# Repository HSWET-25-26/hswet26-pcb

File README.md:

Only edited schematic
Deleted 6v back converter

Schematic
- [x] 1x5 connecter -> 1x4 connector, deleted 6v line
- [x] Resistor and diode are swapped make sure they are swapped - on safety page
- [x] 5V_BUCK label should be 4.5V_BUCK

PCB
- [ ] Trace sizes
    - [ ] Check what gauge traces going into ina (lol it's not nearly what I fixed it for but might as well keep it)
    - [ ] Use larger trace sizes if possible though, no reason not too. And power planes for 9V and turbine for extra safety
- [X] Both of the LM2596 replace with full board
    - [X] Deleted 6v buck converter
- [ ] Add pads for debugging
    - [ ] add Nets:
        - [ ] Linear actuator signal (D5)
        - [ ] Encoder (D2)
        - [ ] Safety signal (D4)
        - [ ] Turbine power 
        - [ ] Lowkey everything there’s not that many nets
- [ ] Add labels to everything!!! on the board! make it as clear as possible
- [ ] Things to double check b/c Mirabel thinks she routed it wrong:
    - [ ] vias on 2 ground pins on U4

- [ ] Add holes on corners for default m3 screws

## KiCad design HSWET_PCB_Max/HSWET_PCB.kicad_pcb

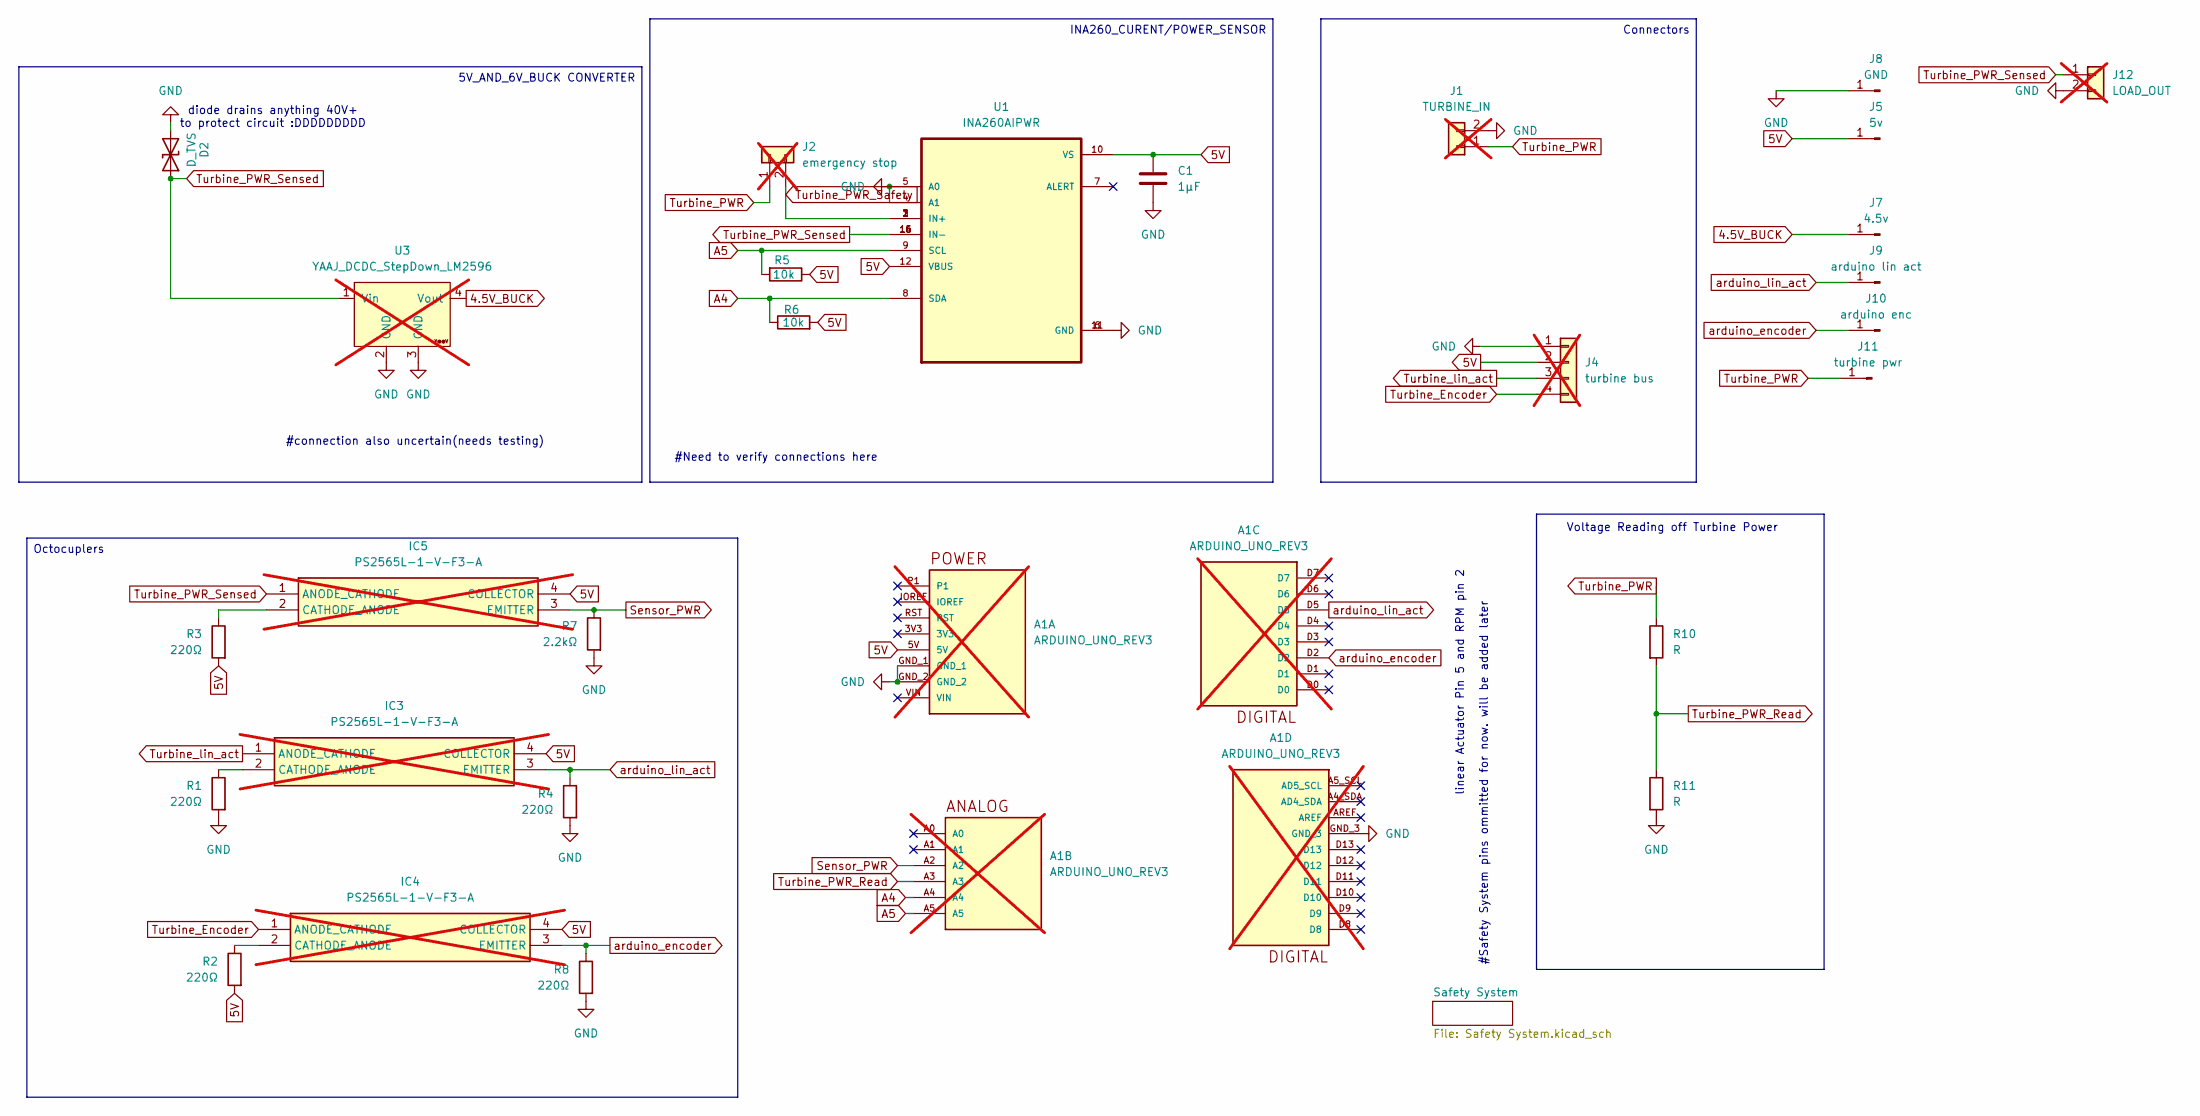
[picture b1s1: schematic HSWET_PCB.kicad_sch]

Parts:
A1: ARDUINO_UNO_REV3; ARDUINO_ARDUINO_UNO_REV3; PARTREV N/A; not fitted
C1: 1µF; C_0603_1608Metric
D2: D_TVS; DIOM4336X265N
IC3, IC4, IC5: PS2565L-1-V-F3-A; DIP762W60P254L460H455Q4N; Manufacturer_Part_Number PS2565L-1-V-F3-A; Mouser Part Number 968-PS2565L-1-V-F3-A; not fitted
J1: TURBINE_IN; AMASS_XT30PW-M_1x02_P2.50mm_Horizontal; not fitted
J2: emergency stop; JST_EH_B2B-EH-A_1x02_P2.50mm_Vertical; not fitted
J4: turbine bus; PinHeader_1x04_P2.54mm_Horizontal; not fitted
J5: 5v; PinHeader_1x01_P1.00mm_Vertical
J7: 4.5v; PinHeader_1x01_P1.00mm_Vertical
J8: GND; PinHeader_1x01_P1.00mm_Vertical
J9: arduino lin act; PinHeader_1x01_P1.00mm_Vertical
J10: arduino enc; PinHeader_1x01_P1.00mm_Vertical
J11: turbine pwr; PinHeader_1x01_P1.00mm_Vertical
J12: LOAD_OUT; AMASS_XT30PW-M_1x02_P2.50mm_Horizontal; not fitted
R1, R2, R3, R4, R8: 220Ω; R_0603_1608Metric
R5, R6: 10k; R_0603_1608Metric
R7: 2.2kΩ; R_0603_1608Metric
R10, R11: R; R_Axial_DIN0207_L6.3mm_D2.5mm_P10.16mm_Horizontal
U1: INA260AIPWR; ina260
U3: YAAJ_DCDC_StepDown_LM2596; not fitted

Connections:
4.5V_BUCK: J7.1, U3.4 (Vout); also elsewhere on the board
A4: A1.A4, R6.1, U1.8 (SDA)
A5: A1.A5, R5.2, U1.9 (SCL)
unnamed: IC3.2 (CATHODE_ANODE), R1.1
unnamed: IC4.2 (CATHODE_ANODE), R2.1
unnamed: IC5.2 (CATHODE_ANODE), R3.1
Sensor_PWR: A1.A2, IC5.3 (EMITTER), R7.1
Turbine_Encoder: IC4.1 (ANODE_CATHODE), J4.4
Turbine_PWR: J1.1, J2.1, J11.1, R10.1
Turbine_PWR_Read: A1.A3, R10.2, R11.1
Turbine_PWR_Safety: J2.2, U1.1 (IN+), U1.2 (IN+), U1.3 (IN+)
Turbine_PWR_Sensed: D2.1 (A1), IC5.1 (ANODE_CATHODE), J12.1, U1.14 (IN-), U1.15 (IN-), U1.16 (IN-), U3.1 (Vin)
Turbine_lin_act: IC3.1 (ANODE_CATHODE), J4.3
arduino_encoder: A1.D2, IC4.3 (EMITTER), J10.1, R8.1
arduino_lin_act: A1.D5, IC3.3 (EMITTER), J9.1, R4.1

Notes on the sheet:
#Safety System pins ommitted for now. will be added later
#Need to verify connections here
#connection also uncertain(needs testing)
linear Actuator Pin 5 and RPM pin 2
Voltage Reading off Turbine Power
diode drains anything 40V+ to protect circuit :DDDDDDDDD
Octocuplers
Connectors
5V_AND_6V_BUCK CONVERTER
INA260_CURENT/POWER_SENSOR

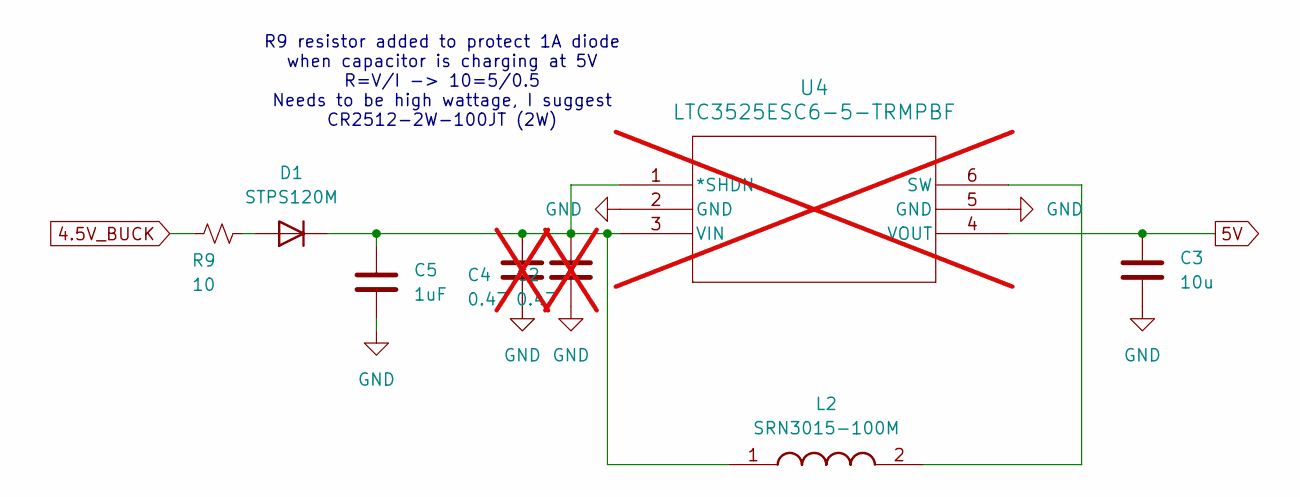
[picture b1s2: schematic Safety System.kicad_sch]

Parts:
C2, C4: 0.47; CAPPRD500W60D1000H3150; not fitted
C3: 10u; C_0603_1608Metric
C5: 1uF; C_0603_1608Metric
D1: STPS120M; DIO_STPS1L40M
L2: SRN3015-100M; SRN3015; Manufacturer_Part_Number SRN3015-100M
R9: 10; R_2512_6332Metric
U4: LTC3525ESC6-5-TRMPBF; SC70-SC6_LIT; not fitted

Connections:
4.5V_BUCK: R9.1; also elsewhere on the board
unnamed: D1.2 (A), R9.2
unnamed: C2.1, C4.1, C5.1, D1.1 (K), L2.1, U4.1 (*SHDN), U4.3 (VIN)
unnamed: L2.2, U4.6 (SW)

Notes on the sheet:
R9 resistor added to protect 1A diode when capacitor is charging at 5V R=V/I -> 10=5/0.5 Needs to be high wattage, I suggest CR2512-2W-100JT (2W)

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
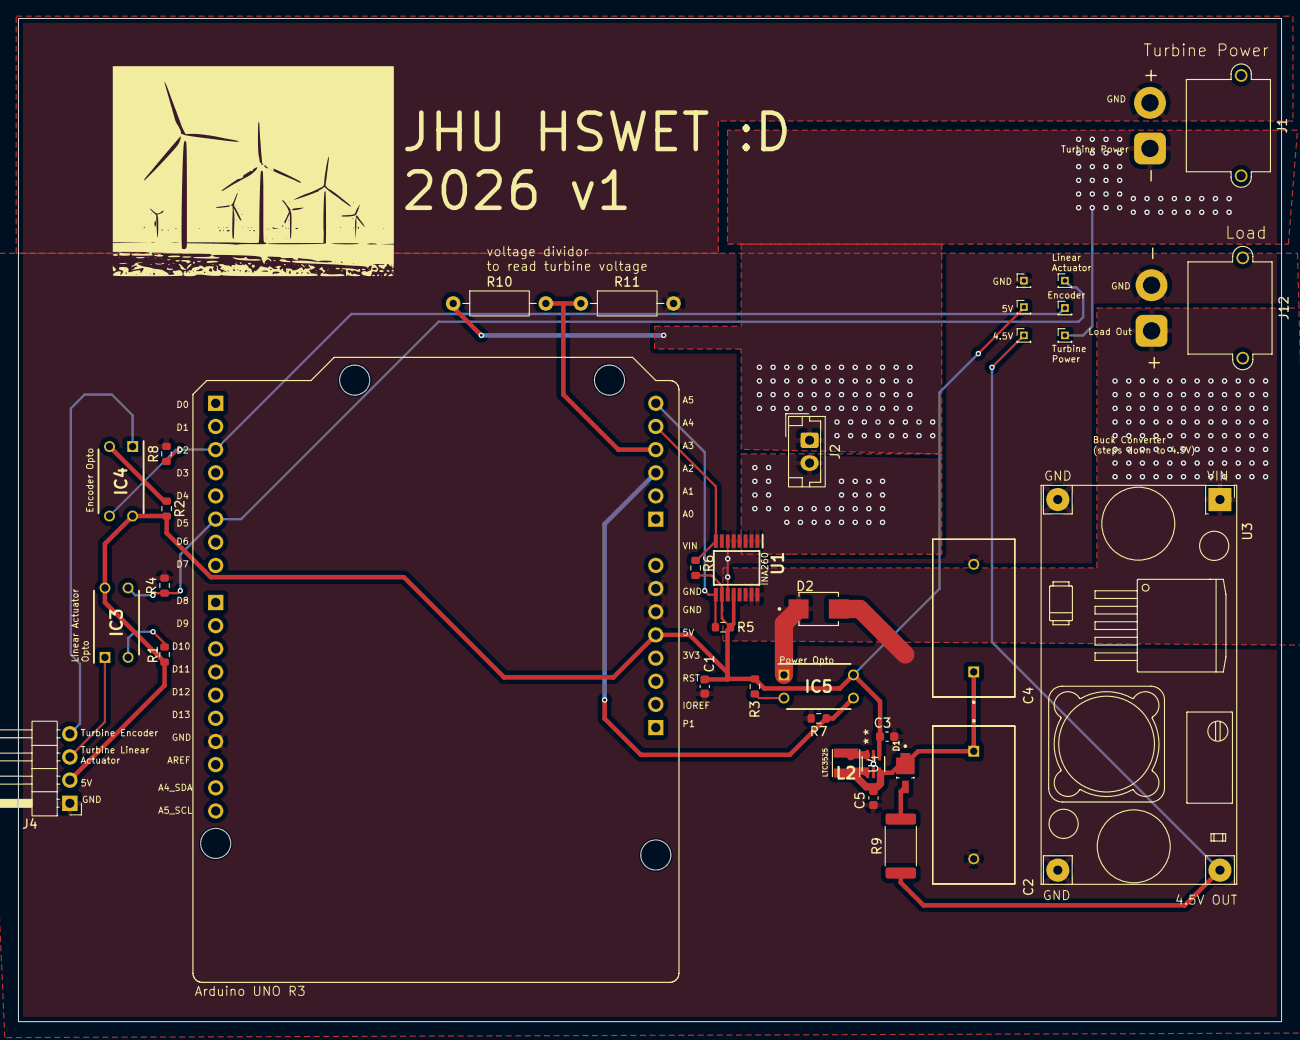
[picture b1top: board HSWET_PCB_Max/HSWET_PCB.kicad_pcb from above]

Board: 2 copper layers, 138.5 x 110.0 mm, 36 parts (0 on the bottom side), 20 nets.

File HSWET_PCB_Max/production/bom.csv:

Designator,Footprint,Quantity,Value,LCSC Part #
C1,0603,1,1µF,
C3,0603,1,10u,
C5,0603,1,1uF,
D1,DIO_STPS1L40M,1,STPS120M,
D2,DIOM4336X265N,1,D_TVS,
J10,PinHeader_1x01_P1.00mm_Vertical,1,arduino enc,
J11,PinHeader_1x01_P1.00mm_Vertical,1,turbine pwr,
J5,PinHeader_1x01_P1.00mm_Vertical,1,5v,
J7,PinHeader_1x01_P1.00mm_Vertical,1,4.5v,
J8,PinHeader_1x01_P1.00mm_Vertical,1,GND,
J9,PinHeader_1x01_P1.00mm_Vertical,1,arduino lin act,
L2,SRN3015,1,SRN3015-100M,
"R1, R2, R3, R4, R8",0603,5,220Ω,
"R10, R11",R_Axial_DIN0207_L6.3mm_D2.5mm_P10.16mm_Horizontal,2,R,
"R5, R6",0603,2,10k,
R7,0603,1,2.2kΩ,
R9,2512,1,10,
U1,ina260,1,INA260AIPWR,

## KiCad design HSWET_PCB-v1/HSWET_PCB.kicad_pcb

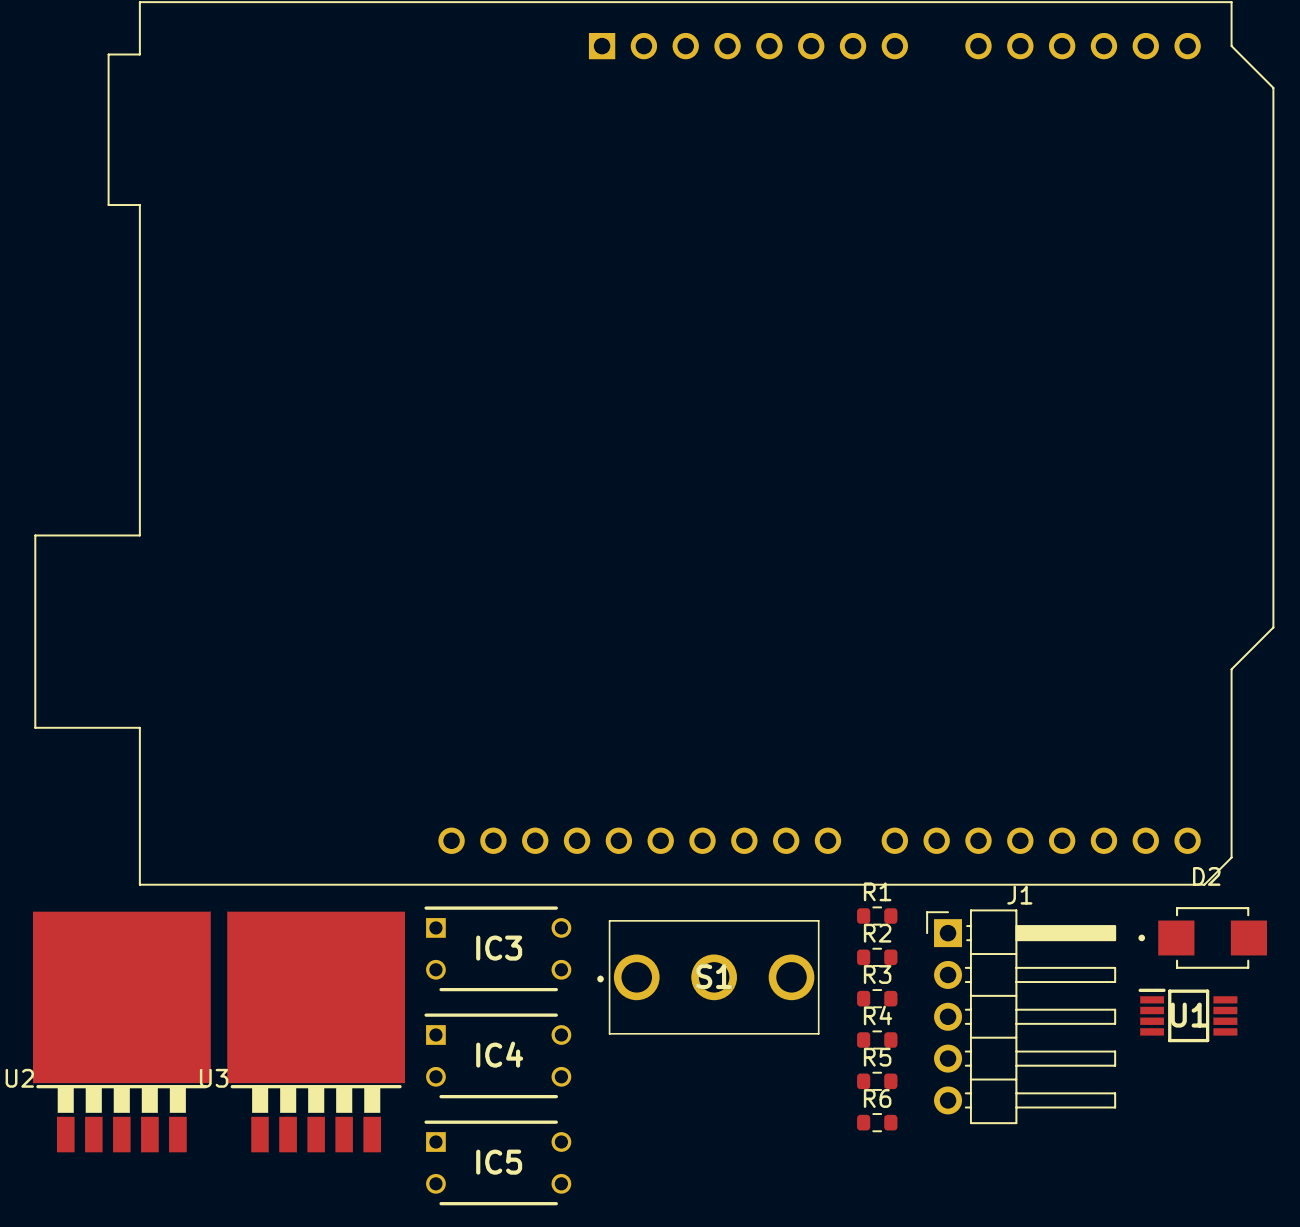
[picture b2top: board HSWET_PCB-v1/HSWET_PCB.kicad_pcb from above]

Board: 2 copper layers, 16 parts (0 on the bottom side), 14 nets, no tracks yet.

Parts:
A1: ARDUINO_UNO_REV3; Arduino_UNO_R3
D2: D_TVS; DIOM4336X265N
IC3, IC4, IC5: PS2565L-1-V-F3-A; DIP762W60P254L460H455Q4N
J1: Conn_01x05_Pin; PinHeader_1x05_P2.54mm_Horizontal
R1, R2, R3, R4, R5, R6: R; R_0603_1608Metric
S1: 100SP1T1B4M2QE
U1: INA260AIPWR; SOP65P490X110-8N
U2, U3: YAAJ_DCDC_StepDown_LM2596; TO263-5

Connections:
5V: IC3.4 (COLLECTOR), IC4.4 (COLLECTOR), J1.2, R1.2, R2.2, R5.2, U3.4 (Vout)
6V: J1.5, U2.4 (Vout)
GND: D2.2 (A2), IC3.1 (ANODE_CATHODE), IC4.1 (ANODE_CATHODE), IC5.1 (ANODE_CATHODE), J1.1, U1.6 (GND), U2.2 (GND), U2.3 (GND), U3.2 (GND), U3.3 (GND)
unnamed: U1.1 (IN+), U1.2 (IN+), U1.3 (IN+)
unnamed: IC3.2 (CATHODE_ANODE), R1.1
unnamed: IC3.3 (EMITTER), R4.1
unnamed: IC4.2 (CATHODE_ANODE), R2.1
unnamed: IC4.3 (EMITTER), R3.1
unnamed: IC5.2 (CATHODE_ANODE), R5.1
unnamed: IC5.3 (EMITTER), R6.1
unnamed: S1.2, U2.1 (Vin), U3.1 (Vin)
PWR: D2.1 (A1), R6.2, S1.3
RPM: J1.3, R3.2
lin_act: J1.4, R4.2

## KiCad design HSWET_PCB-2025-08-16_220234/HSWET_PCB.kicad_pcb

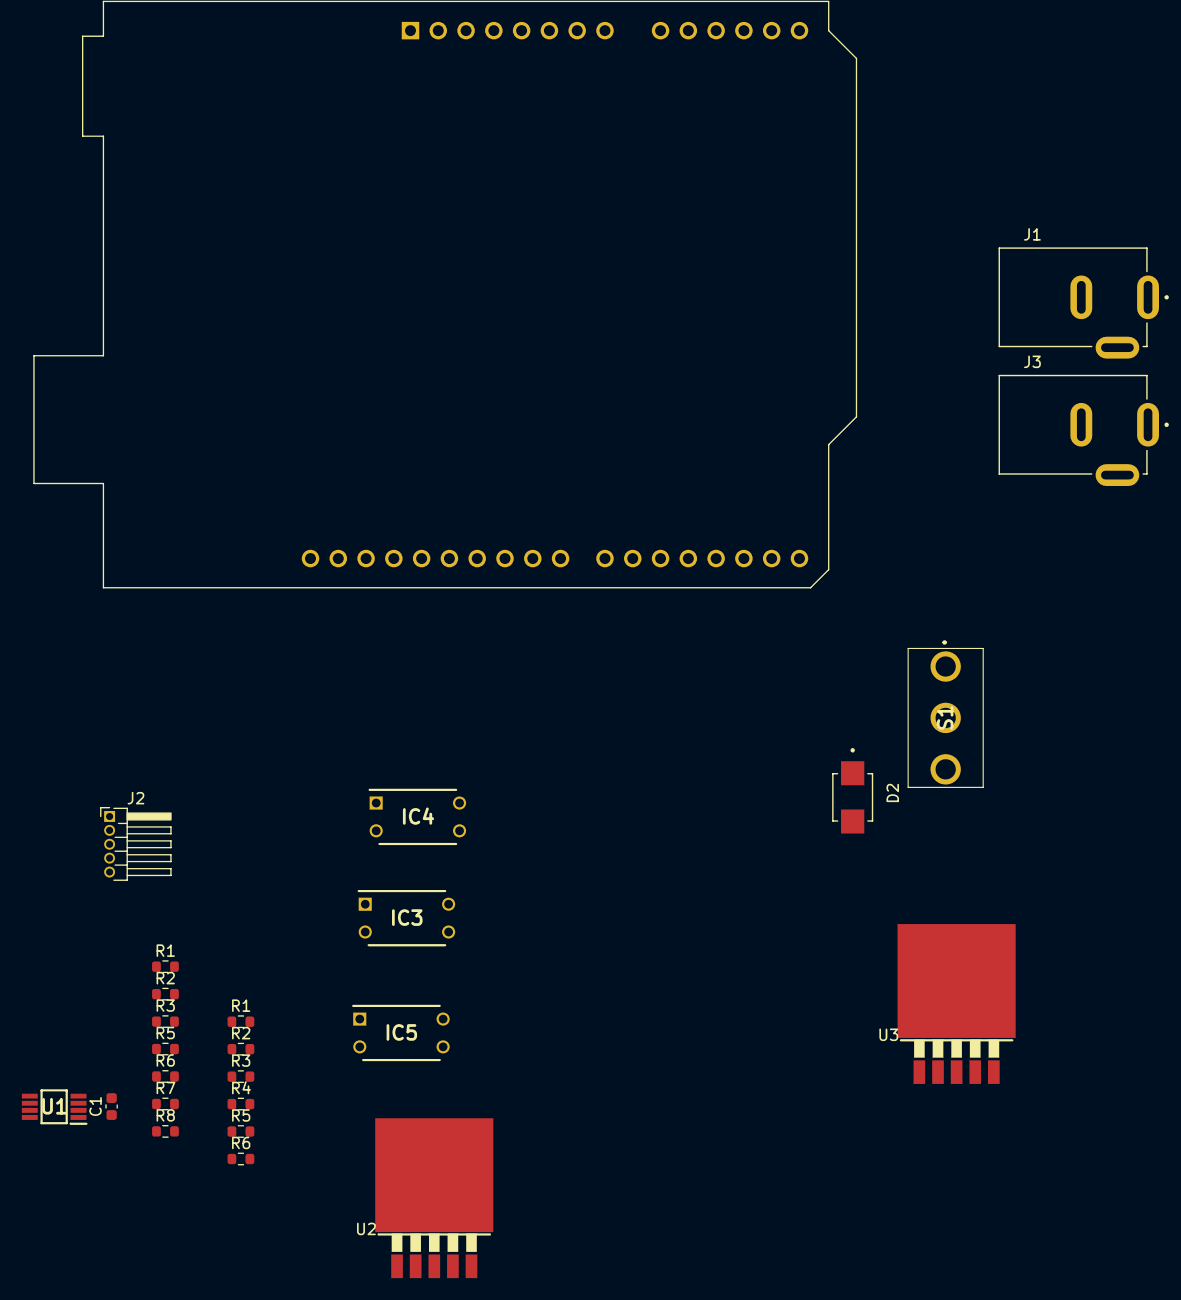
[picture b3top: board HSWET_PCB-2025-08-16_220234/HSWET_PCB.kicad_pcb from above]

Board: 2 copper layers, 26 parts (0 on the bottom side), 14 nets, no tracks yet.

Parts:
A1: ARDUINO_UNO_REV3; Arduino_UNO_R3
C1: 1µF; C_0603_1608Metric
D2: D_TVS; DIOM4336X265N
IC3, IC4, IC5: PS2565L-1-V-F3-A; DIP762W60P254L460H455Q4N
J1, J3: CON-SOCJ-2155; GRAVITECH_CON-SOCJ-2155
J2: Conn_01x05; PinHeader_1x05_P1.27mm_Horizontal
R1, R2#2, R3, R4, R8: 220Ω; R_0603_1608Metric
R1#2, R2, R3#2, R5, R6#2: R; R_0603_1608Metric
R5#2, R6: 10k; R_0603_1608Metric
R7: 2.2kΩ; R_0603_1608Metric
S1: 100SP1T1B4M2QE
U1: INA260AIPWR; SOP65P490X110-8N
U2, U3: YAAJ_DCDC_StepDown_LM2596; TO263-5

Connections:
5V: C1.2, IC3.4 (COLLECTOR), IC4.4 (COLLECTOR), IC5.4 (COLLECTOR), J2.3, R1.2, R1#2.2, R2.2, R2#2.2, R3.2, R5.2, R5#2.1, R6.2, U3.4 (Vout)
6V: J2.2, U2.4 (Vout)
9V: J3.1, S1.1
A4: R6.1, U1.8 (SDA)
GND: C1.1, D2.2 (A2), J1.3, J2.1, J3.3, R4.2, R7.2, R8.2, U1.4 (A1), U1.5 (A0), U1.6 (GND), U2.2 (GND), U2.3 (GND), U3.2 (GND), U3.3 (GND)
unnamed: IC3.2 (CATHODE_ANODE), R1.1, R1#2.1
unnamed: IC4.2 (CATHODE_ANODE), R2.1, R2#2.1
unnamed: IC5.2 (CATHODE_ANODE), R3.1, R5.1
unnamed: S1.2, U2.1 (Vin), U3.1 (Vin)
Sensor_PWR: IC5.3 (EMITTER), R7.1
Turbine_Encoder: IC4.1 (ANODE_CATHODE), J2.5
Turbine_PWR: D2.1 (A1), IC5.1 (ANODE_CATHODE), J1.1, S1.3, U1.1 (IN+), U1.2 (IN+), U1.3 (IN+)
arduino_encoder: IC4.3 (EMITTER), R8.1
arduino_lin_act: IC3.3 (EMITTER), R4.1

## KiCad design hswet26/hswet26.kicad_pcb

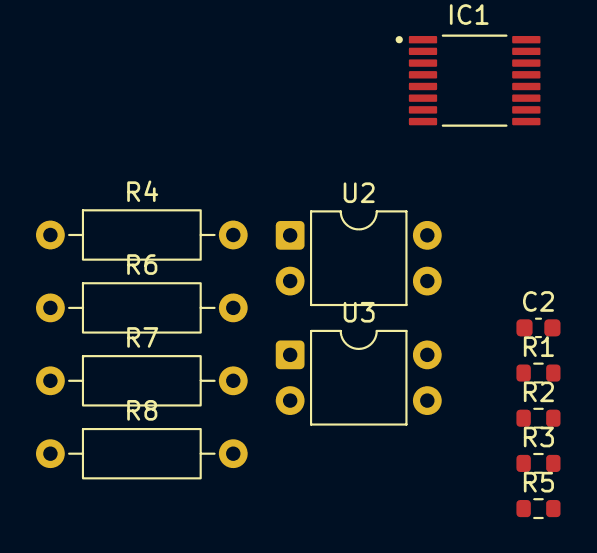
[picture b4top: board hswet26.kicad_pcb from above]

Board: 2 copper layers, 12 parts (0 on the bottom side), 12 nets, no tracks yet.

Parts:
C2: 1uF; C_0603_1608Metric
IC1: INA260; SOP65P640X120-16N
R1, R2, R3, R5: 0603 10k; R_0603_1608Metric
R4, R7, R8: 220ohm 1/4W; R_Axial_DIN0207_L6.3mm_D2.5mm_P10.16mm_Horizontal
R6: 2.2kOhm 1/4W; R_Axial_DIN0207_L6.3mm_D2.5mm_P10.16mm_Horizontal
U2, U3: PC817; DIP-4_W7.62mm

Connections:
+5V: C2.1, IC1.10 (VS), R1.1, R2.1, U2.4, U3.4
/A0: IC1.5 (A0), R5.1
/A1: IC1.4 (A1), R3.1
/ARDUINO-LINEAR-ACTUATOR: R8.2, U3.3
/ARDUINO_ENCODER: R6.2, U2.3
/SCL: IC1.9 (SCL), R1.2
/SDA: IC1.8 (SDA), R2.2
GND: C2.2, IC1.6 (GND), IC1.11 (GND), IC1.13 (GND), R3.2, R4.1, R5.2, R6.1, R7.1, R8.1
unnamed: IC1.1 (IN+), IC1.2 (IN+), IC1.3 (IN+)
unnamed: IC1.14 (IN-), IC1.15 (IN-), IC1.16 (IN-)
unnamed: R4.2, U2.2
unnamed: R7.2, U3.2

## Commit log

2025-12-10 initiali push WARNING I MESSED UP ALL RELATIVE FILES LOLOLOL
2026-02-10 fixed some footprints (added another folder
2026-02-10 Add WIP note and warning to README
    Added a work-in-progress note and a warning about file paths.
2026-02-10 updated footprints
2026-02-20 layout changes
2026-02-24 shcematic: git add . e0f
    ?
2026-02-27 routing done
2026-03-03 trying to link symbol lib
2026-03-03 trying to resolve symbol issues
2026-03-03 merging
2026-03-08 Updating Schematic
2026-03-08 git add HSWET_PCB_Max/sym-lib-table
2026-03-08 Integrated safety
2026-03-08 Completed layout for safety system
2026-03-08 updating footprint files
2026-03-09 modified for access
2026-03-10 pushing one added cap
2026-03-10 swithced resistor and diode
2026-03-10 lucas own branch
2026-03-10 added maybe unecessary plane, swapped 1x05 connector -> 1x04 after mirabel got rid of 6v, ficed footprint for lm2596
2026-03-10 Revise schematic and PCB details in README
    Updated schematic and PCB notes in README.md, including deletions and modifications.
2026-03-10 new routing for pcb, some smaller ports still unrouted
2026-03-11 added diagrams and small changes
2026-03-11 labelled everything, cleanup up various things, corrected inductor, removed schmitt
2026-03-11 this is the ersion we made gerbers for
2026-03-12 bruh
2026-03-12 made traces for power muuuuuuuuuuuuch bigger and added connector for load and removed 9v stuff just plug into the turbine
2026-04-19 fixed lin act schematci
